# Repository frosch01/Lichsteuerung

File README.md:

# Lichtsteuerung

## Hardware setup

Prepare you PI for the S0-Shield by adding GPIO configuration to the config.txt.

```
echo "
# GPIO and PWM configuration for S0 shield
dtoverlay=pwm,pin=13,func=4,clock=500000
gpio=4,5,6,17,19,22,26,27=ip,pu
gpio=12,16,18,20,21,23,24,25=op,dh
" | sudo tee -a /boot/config.txt

```

For development, not using a PI Zero, a different IO setup is in use as Pins
of newer PI designs is different and there is a line collision with EPROM.

```
echo "
# GPIO and PWM configuration for S0 shield
dtoverlay=pwm,pin=13,func=4,clock=500000
gpio=15,5,6,17,19,22,26,27=ip,pu
gpio=12,16,18,20,21,23,24,25=op,dh
" | sudo tee -a /boot/config.txt
```

## Amount of Meter Pulses per year

One HVAC takes about 300kwh per year. This means 300k pulses. 3 HVAC systems 
result in <1M pulses per year.

In the log, a world timestamp, and the power shall be stored. The 
timestamp takes 11 bytes including space 11. The power takes 5 bytes including
newline. So 16 bytes to store. Let's go for 20 in calculation....

Amount of bytes expected per year: 20MByte

It seems to be feasible to keep a cache inside the program for online visualization.

Big data part should be kept separated from the tool.

For fast search a FS based directory structure based on year, and month with a file 
per day seems to be a valid data base idea.

TinyFLux seems to be a nice idea to use as a file based time series DB.

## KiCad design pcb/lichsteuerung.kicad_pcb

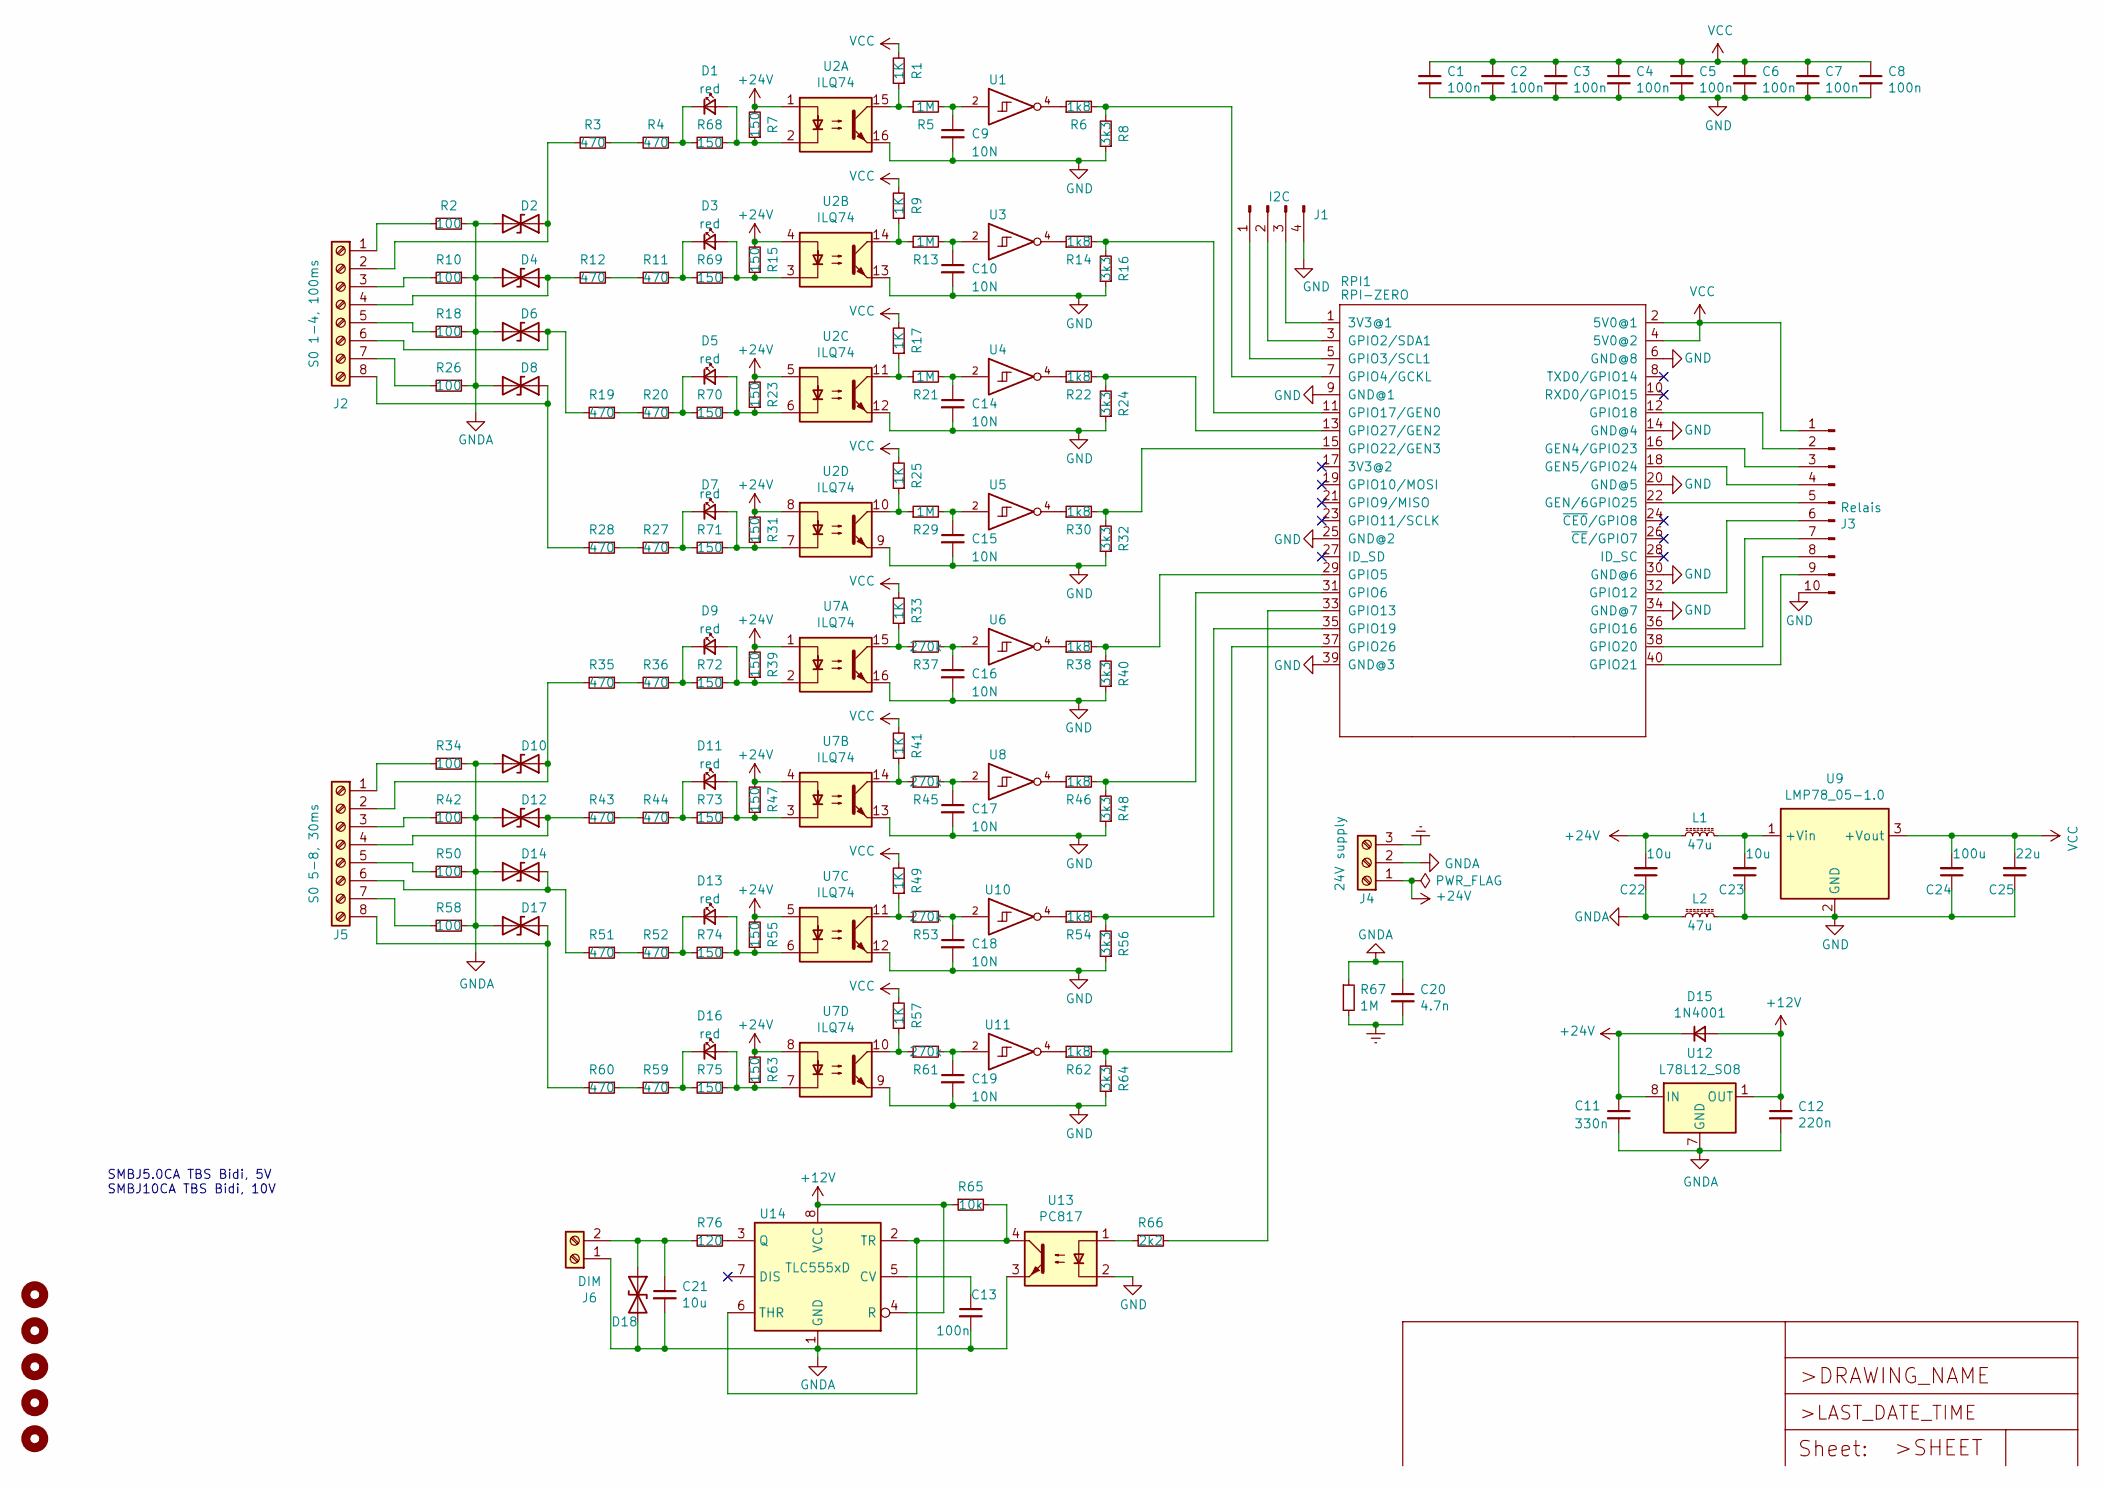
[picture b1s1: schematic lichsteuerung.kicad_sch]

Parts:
C1, C2, C3, C4, C5, C6, C7, C8, C13: 100n; C_0805_2012Metric_Pad1.18x1.45mm_HandSolder
C9, C10, C14, C15, C16, C17, C18, C19: 10N; C_0805_2012Metric_Pad1.18x1.45mm_HandSolder
C11: 330n; C_0805_2012Metric_Pad1.18x1.45mm_HandSolder
C12: 220n; C_0805_2012Metric_Pad1.18x1.45mm_HandSolder
C20: 4.7n; C_0805_2012Metric_Pad1.18x1.45mm_HandSolder
C21, C22, C23: 10u; C_1210_3225Metric_Pad1.33x2.70mm_HandSolder
C24: 100u; C_1210_3225Metric_Pad1.33x2.70mm_HandSolder
C25: 22u; C_1210_3225Metric_Pad1.33x2.70mm_HandSolder
D1, D3, D5, D7, D9, D11, D13, D16: red; LED_1206_3216Metric_Pad1.42x1.75mm_HandSolder
D2, D4, D6, D8, D10, D12, D14, D17: 24V; D_SMB
D15: 1N4001; D_SOD-123
D18: 12V; D_SMB
H1, H2, H3, H4, H5: MountingHole; MountingHole_3.2mm_M3_DIN965
J1: I2C; PinHeader_1x04_P2.54mm_Vertical
J2: S0 1-4, 100ms; TerminalBlock_Phoenix_MKDS-1,5-8-5.08_1x08_P5.08mm_Horizont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
J3: Relais; Molex_KK-254_AE-6410-10A_1x10_P2.54mm_Vertical
J4: 24V supply; TerminalBlock_Phoenix_MKDS-1,5-3-5.08_1x03_P5.08mm_Horizont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
J5: S0 5-8, 30ms; TerminalBlock_Phoenix_MKDS-1,5-8-5.08_1x08_P5.08mm_Horizont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
J6: DIM; TerminalBlock_Phoenix_MKDS-1,5-2-5.08_1x02_P5.08mm_Horizont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
L1, L2: 47u; L_1812_4532Metric_Pad1.30x3.40mm_HandSolder
R1, R9, R17, R25, R33, R41, R49, R57: 1K; R_0805_2012Metric_Pad1.20x1.40mm_HandSolder
R2, R10, R18, R26, R34, R42, R50, R58: 100; R_0805_2012Metric_Pad1.20x1.40mm_HandSolder
R3, R4, R11, R12, R19, R20, R27, R28, R35, R36, R43, R44, R51, R52, R59, R60: 470; R_1206_3216Metric_Pad1.30x1.75mm_HandSolder
R5, R13, R21, R29, R67: 1M; R_0805_2012Metric_Pad1.20x1.40mm_HandSolder
R6, R14, R22, R30, R38, R46, R54, R62: 1k8; R_0805_2012Metric_Pad1.20x1.40mm_HandSolder
R7, R15, R23, R31, R39, R47, R55, R63, R68, R69, R70, R71, R72, R73, R74, R75: 150; R_0805_2012Metric_Pad1.20x1.40mm_HandSolder
R8, R16, R24, R32, R40, R48, R56, R64: 3k3; R_0805_2012Metric_Pad1.20x1.40mm_HandSolder
R37, R45, R53, R61: 270k; R_0805_2012Metric_Pad1.20x1.40mm_HandSolder
R65: 10k; R_0805_2012Metric_Pad1.20x1.40mm_HandSolder
R66: 2k2; R_0805_2012Metric_Pad1.20x1.40mm_HandSolder
R76: 120; R_0805_2012Metric_Pad1.20x1.40mm_HandSolder
RPI1: RPI-ZERO; RASPBERRYPI_BASTELSTUBE_V13_RASPI_BOARD_ZERO_FULL
U1, U3, U4, U5, U6, U8, U10, U11: 74LVC1G14; SOT-23-5_HandSoldering
U2, U7: ILQ74; DIP-16_W7.62mm_LongPads
U9: LMP78_05-1.0; Converter_DCDC_Gaptech_LMx78_xx_1.0_THT
U12: L78L12_SO8; SOIC-8_3.9x4.9mm_P1.27mm
U13: PC817; DIP-4_W7.62mm_LongPads
U14: TLC555xD; SOIC-8_3.9x4.9mm_P1.27mm

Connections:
+12V: C12.1, D15.2 (A), R65.1, U12.1 (OUT), U14.4 (R), U14.8 (VCC)
+24V: C11.1, C22.2, D15.1 (K), J4.1, L1.1, R7.2, R15.2, R23.2, R31.2, R39.2, R47.2, R55.2, R63.2, U2.1, U2.4, U2.5, U2.8, U7.1, U7.4, U7.5, U7.8, U12.8 (IN)
Earth: C20.2, J4.3, R67.2
GND: C1.2, C2.2, C3.2, C4.2, C5.2, C6.2, C7.2, C8.2, C9.2, C10.2, C14.2, C15.2, C16.2, C17.2, C18.2, C19.2, C23.1, C24.1, C25.1, J1.4, J3.10, L2.2, R8.1, R16.1, R24.1, R32.1, R40.1, R48.1, R56.1, R64.1, RPI1.6 (GND@8), RPI1.9 (GND@1), RPI1.14 (GND@4), RPI1.20 (GND@5), RPI1.25 (GND@2), RPI1.30 (GND@6), RPI1.34 (GND@7), RPI1.39 (GND@3), U1.3 (GND), U2.9, U2.12, U2.13, U2.16, U3.3 (GND), U4.3 (GND), U5.3 (GND), U6.3 (GND), U7.9, U7.12, U7.13, U7.16, U8.3 (GND), U9.2 (GND), U10.3 (GND), U11.3 (GND), U13.2
GNDA: C11.2, C12.2, C13.2, C20.1, C21.2, C22.1, D2.2 (A2), D4.2 (A2), D6.2 (A2), D8.2 (A2), D10.2 (A2), D12.2 (A2), D14.2 (A2), D17.2 (A2), D18.2 (A2), J4.2, J6.1, L2.1, R2.1, R10.1, R18.1, R26.1, R34.1, R42.1, R50.1, R58.1, R67.1, U12.2 (GND), U12.3 (GND), U12.6 (GND), U12.7 (GND), U13.3, U14.1 (GND)
unnamed: C9.1, R5.2, U1.2
unnamed: C10.1, R13.2, U3.2
unnamed: C13.1, U14.5 (CV)
unnamed: C14.1, R21.2, U4.2
unnamed: C15.1, R29.2, U5.2
unnamed: C16.1, R37.2, U6.2
unnamed: C17.1, R45.2, U8.2
unnamed: C18.1, R53.2, U10.2
unnamed: C19.1, R61.2, U11.2
unnamed: C21.1, D18.1 (A1), J6.2, R76.2
unnamed: C23.2, L1.2, U9.1 (+Vin)
unnamed: D1.1 (K), R4.1, R68.2
unnamed: D1.2 (A), R7.1, R68.1, U2.2
unnamed: D2.1 (A1), J2.2, R3.2
unnamed: D3.1 (K), R11.1, R69.2
unnamed: D3.2 (A), R15.1, R69.1, U2.3
unnamed: D4.1 (A1), J2.4, R12.2
unnamed: D5.1 (K), R20.1, R70.2
unnamed: D5.2 (A), R23.1, R70.1, U2.6
unnamed: D6.1 (A1), J2.6, R19.2
unnamed: D7.1 (K), R27.1, R71.2
unnamed: D7.2 (A), R31.1, R71.1, U2.7
unnamed: D8.1 (A1), J2.8, R28.2
unnamed: D9.1 (K), R36.1, R72.2
unnamed: D9.2 (A), R39.1, R72.1, U7.2
unnamed: D10.1 (A1), J5.2, R35.2
unnamed: D11.1 (K), R44.1, R73.2
unnamed: D11.2 (A), R47.1, R73.1, U7.3
unnamed: D12.1 (A1), J5.4, R43.2
unnamed: D13.1 (K), R52.1, R74.2
unnamed: D13.2 (A), R55.1, R74.1, U7.6
unnamed: D14.1 (A1), J5.6, R51.2
unnamed: D16.1 (K), R59.1, R75.2
unnamed: D16.2 (A), R63.1, R75.1, U7.7
unnamed: D17.1 (A1), J5.8, R60.2
unnamed: J1.1, RPI1.5 (GPIO3/SCL1)
unnamed: J1.2, RPI1.3 (GPIO2/SDA1)
unnamed: J1.3, RPI1.1 (3V3@1)
unnamed: J2.3, R10.2
unnamed: J2.5, R18.2
unnamed: J2.7, R26.2
unnamed: J5.1, R34.2
unnamed: J5.3, R42.2
unnamed: J5.5, R50.2
unnamed: J5.7, R58.2
unnamed: R1.1, R5.1, U2.15
unnamed: J2.1, R2.2
unnamed: R3.1, R4.2
unnamed: R6.1, U1.4
unnamed: R6.2, R8.2, RPI1.7 (GPIO4/GCKL)
unnamed: R11.2, R12.1
unnamed: R9.1, R13.1, U2.14
unnamed: R14.1, U3.4
unnamed: R14.2, R16.2, RPI1.11 (GPIO17/GEN0)
unnamed: R17.1, R21.1, U2.11
unnamed: R19.1, R20.2
unnamed: R22.1, U4.4
unnamed: R22.2, R24.2, RPI1.13 (GPIO27/GEN2)
unnamed: R25.1, R29.1, U2.10
unnamed: R27.2, R28.1
unnamed: R30.1, U5.4
unnamed: R30.2, R32.2, RPI1.15 (GPIO22/GEN3)
unnamed: R33.1, R37.1, U7.15
unnamed: R35.1, R36.2
unnamed: R38.1, U6.4
unnamed: R38.2, R40.2, RPI1.29 (GPIO5)
unnamed: R41.1, R45.1, U7.14
unnamed: R43.1, R44.2
unnamed: R46.1, U8.4
unnamed: R46.2, R48.2, RPI1.31 (GPIO6)
unnamed: R49.1, R53.1, U7.11
unnamed: R51.1, R52.2
unnamed: R54.1, U10.4
unnamed: R54.2, R56.2, RPI1.35 (GPIO19)
unnamed: R57.1, R61.1, U7.10
unnamed: R59.2, R60.1
unnamed: R62.1, U11.4
unnamed: R62.2, R64.2, RPI1.37 (GPIO26)
unnamed: R65.2, U13.4, U14.2 (TR), U14.6 (THR)
unnamed: R66.1, U13.1
unnamed: R66.2, RPI1.33 (GPIO13)
unnamed: R76.1, U14.3 (Q)
unnamed: J3.2, RPI1.12 (GPIO18)
unnamed: J3.3, RPI1.16 (GEN4/GPIO23)
unnamed: J3.4, RPI1.18 (GEN5/GPIO24)
unnamed: J3.5, RPI1.22 (GEN/6GPIO25)
unnamed: J3.6, RPI1.32 (GPIO12)
unnamed: J3.7, RPI1.36 (GPIO16)
unnamed: J3.8, RPI1.38 (GPIO20)
unnamed: J3.9, RPI1.40 (GPIO21)
VCC: C1.1, C2.1, C3.1, C4.1, C5.1, C6.1, C7.1, C8.1, C24.2, C25.2, J3.1, R1.2, R9.2, R17.2, R25.2, R33.2, R41.2, R49.2, R57.2, RPI1.2 (5V0@1), RPI1.4 (5V0@2), U1.5 (VCC), U3.5 (VCC), U4.5 (VCC), U5.5 (VCC), U6.5 (VCC), U8.5 (VCC), U9.3 (+Vout), U10.5 (VCC), U11.5 (VCC)

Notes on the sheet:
SMBJ5.0CA TBS Bidi, 5V SMBJ10CA TBS Bidi, 10V

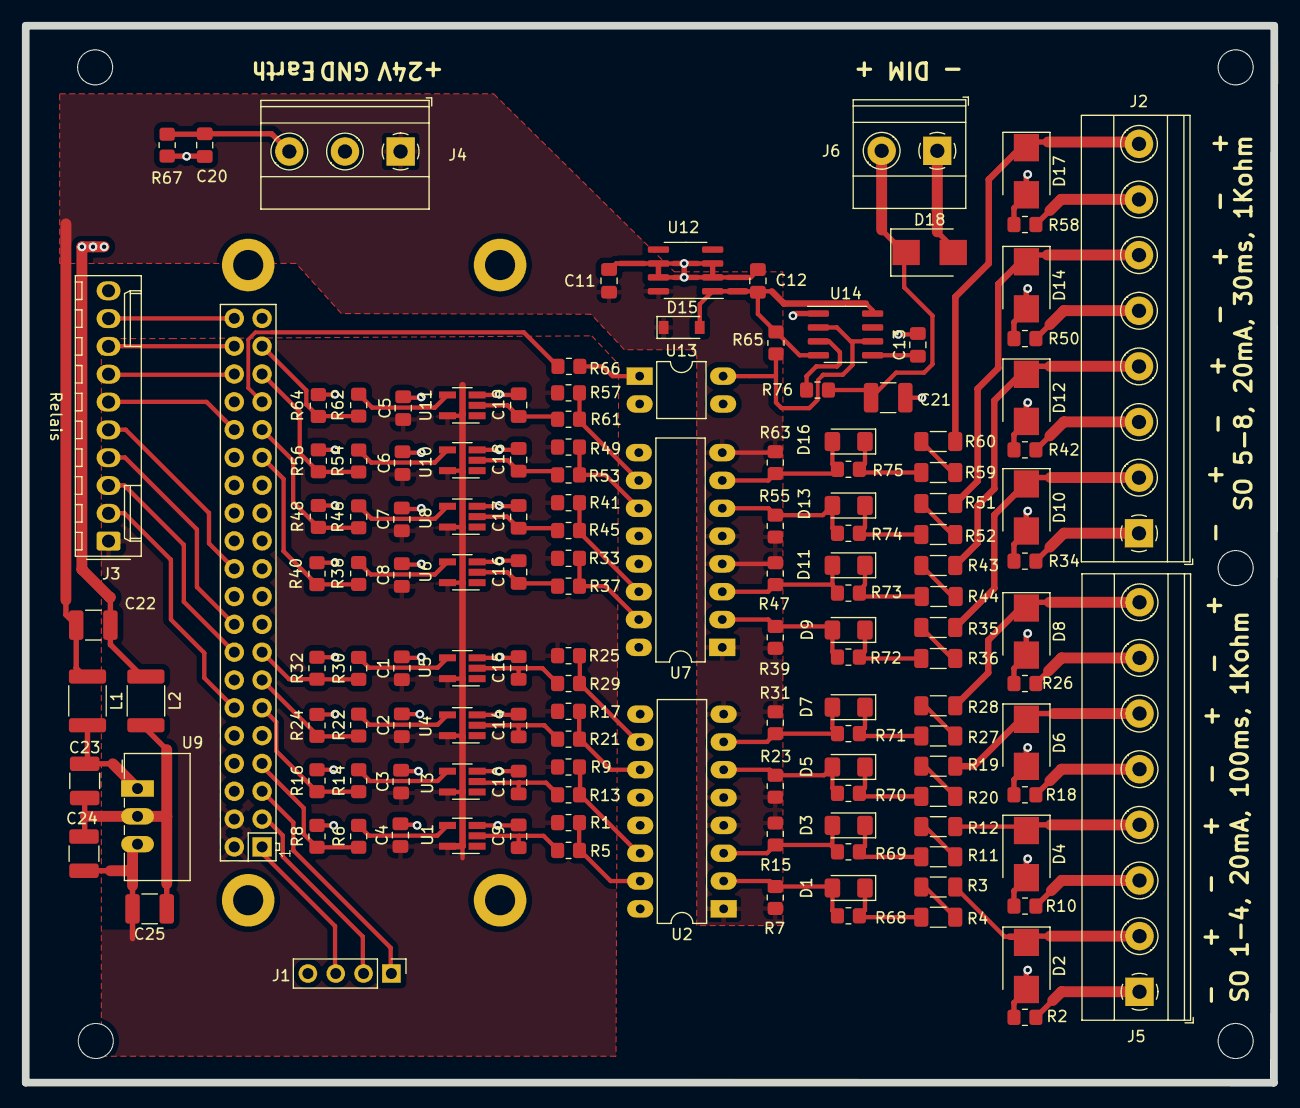
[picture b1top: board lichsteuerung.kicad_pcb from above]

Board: 2 copper layers, 114.0 x 96.5 mm, 147 parts (0 on the bottom side), 96 nets.

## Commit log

2017-06-14 ADDED: Test script for relais test
2017-06-15 ADDED: Readme.md, empty for now
2017-06-15 ADDED: little pwm test
2017-06-18 ADDED: Python based device access using wiringpi
2017-06-27 CHANGED: Design adapted towards better OO concepts. A singleton aproach seems to meet basic IO best
2017-06-27 CHANGED: Design to be more pythonic and more object oriented.
2017-06-27 FIXED: Removed vertical spaces
2017-06-27 CHANGED: Removed dependency from global gpio object.
2017-07-02 ADDED: Simple test from flexx button API documentation.
2017-07-02 CHANGED: Location of test/demo programs
2017-07-02 CHANGED: Switch to Python asyncio event handling
2017-07-02 CHANGED: Timing changed to absolute timing
2017-07-03 CHANGED: Relais timed on state implemented into own class
2017-07-03 ADDED: Added time until relais On
2017-07-05 ADDED: First Web UI
2017-07-07 ADDED: Stub GPIO module to be able to also run on X86
2017-07-07 FIXED. Py detection
2017-07-07 ADDED: Threading for asyncio GPIO
2017-07-07 FIXED: Exiting
2017-07-07 ADDED: print
2017-07-08 CHANGED: GPIO instance belongs now to LightControl
2017-07-08 FIXED: Missing file from previous commit.
2017-07-08 CHANGED: Main moved into light_ui.py for easier connecting UI with light_control
2017-07-09 ADDED: Made light_control to react on light UI.
2017-07-09 CHANGED: Switched to using events instead of properties as event are more versatile
2017-07-09 FIXED: Auto mode is default off
2017-07-09 ADDED: Enhanced event handling to all the Lamps
2017-07-09 FIXED: Override behavior of automatic mode
2017-07-09 ADDED: Action log printing
2017-07-09 ADDED: Handling of detectors from UI
2017-07-09 FIXED: variable referencing
2017-07-09 ADDED: PWM initialized
2017-07-09 FIXED: Bad parameters
2017-07-09 ADDED: PWM support. Needs root to execute
2017-07-10 CHANGED: Flexx Events are now handled by Python class instead of JS class
2017-07-10 ADDED: Determination of night and day from clock
2017-08-08 ADDED: Reflect current mode as UI is started
2017-08-09 CHANGED: Lamp to relais assignment
2017-08-09 CHANGED: Input assignment
2017-08-09 CHANGED: PWM range
2017-08-09 ADDED: Light activation limited to night!
2017-08-10 ADDED: Setting of default modes at 06:00
2017-08-10 FIXED: Made output unbuffered to get outputs immediatly into system logs when runniung as daemon
2023-01-06 Added updated PCB
2023-01-06 Added .gitignore
2023-12-25 Add documentation how RPI HW setup
2023-12-25 Run pylint, clear errors
    Focus is given to class IoControl which is intended to be pushed into a
    separate module.
2024-01-04 ✨ Add io_control for new HW shield
    Implemented based on Python 3.11 and gpiod using libgpiod 2.1.x.
2024-01-04 Create pylint.yml
    Add runner for pylint
2024-01-04 Create python-app.yml
    Add pytest CI automation
2024-01-04 ✨ Add s0 energy metering
    S0 is a pulse based interface. It is found on many energy meters. The
    implementation is based on a software counter. By derivating the pulses
    over time, the power consumption is calculated.
2024-01-04 💚 Fix python application workflow
    Fixed:
    - missing mock package
2024-01-05 🚚 Push low level GPIO into dedicated class
    Part 1 of separating low level access and high level acces of I/O control
    into 2 classes.
2024-02-03 ♻️ Refactor GpioMap and prepare for testing
    Focus on low level I/O only. Remove all async code from the class. Add
    API documentation.
2024-02-03 ✅ Add GpioMap testing
    Add test for low level HW access testing. Tests will only run on HW
    that has a shield connected. Also, the S0 inputs must be connected to
    the relais.
2024-02-03 ⚗️ Add experiment for fast list member check
    What is faster? Using 'in' on a list directly or via a helper dict.
2024-02-03 💚 Fix CI after refactoring
2024-02-03 🏗️ Re-add io_control.py as 2nd level abstraction
    io_control shall take the job to distinguish detector and meter inputs
    and provide asyncio interfaces as required.
2024-02-03 ✨ Add UI based on nicegui
2024-02-03 ✨ Integrate meter with IoControl
2024-02-03 📝 Add some thoughts on logging
2024-02-03 ⚗️ Verify approach of I/O thread
2024-02-03 ✨ Add new class Timespan
    Timespan is intended to represent a span of time given by a start point
    and an end point in time. It can be used with any clock.
2024-02-03 🧵 Add asyncio interface to S0Meter class
    Add ayncio.Queue based processing of S0Events.
2024-02-03 🧵 Convert IoControl into generic S0Eventhandler
    Provide an async integration of meters with s0 event handler.
2024-02-03 ✨ Add TimedRelais class
    TimedRelais is a class to turn relais on and off given by a timed
    schedule.
2024-02-03 💡 Add documentation on modules and classes
    More words on s0_meter.py and io_control.py.
2024-02-03 ♻️ Spawn event handler tasks implicitly
    Having all these event handler tasks at the top level is anoying. Tasks
    are spawned implicitly by __init__.
2024-02-03 ✨ Add time/location based sun sensor
    A daylight sensor based on the idea that sunset and sunrise can be
    determined by location and local time.
2024-04-07 ✨ Couple UI with I/O
    First working new design. As of now, based on a global/singleton
    based architecture, but all features from the previous implementation
    are included.
2024-04-07 🧱 Add systemd service file
    The light-control shall be executed automatically on boot.
2024-04-07 🩹 Adapt on times of lamps
    The former values have been set for playing in lab. On times
    were very short which creates high wear on LED lights. Longer
    on times will let last lamps longer.
2024-05-26 ✨ Add storing of meters in state file
    Application states are stored at /var/lib/light-control/state.json.
2024-05-26 ✨ Add calibration inputs to UI
    It is convenient to read the meters and directly input the displayed
    values as calibration value for the local energy counters.
2024-05-26 ✨ Add dimmer support
    Lamp on terrace has a dimmer. Enable dimming. UI had already the
    element, however it was just an UI element.
2024-05-26 🔥 Remove obsolte files
2024-05-26 ✅ Add test
    More tests added
2024-05-26 🩹 Increaded on times for lamps
    LED lights have limited number of on-off cycles. Increaing the times
    reduces the wear of lamps.
2024-05-26 🙈 Update .gitignore
2024-06-22 ✨ Add detection of board version
    PI Zero and regular PI boards have a different assignment of GPIO Pins.
    Unfortuately, one PIN was selected on Zero that was not available on
    PI4. So a Board_type detection was added.
2024-06-22 ⚗️ Add some basic API checks
    Add some little examples on how to deal with asyncio events (SW) and
    how to use the Raspi HW PWM.
2024-06-22 🚚 Rename directory test into experiments
2024-06-22 ⬆️ Update requirments.txt
2026-01-02 🐛 Fix instantiation if light_ui singleton
    This fix was required due to a change of upstream nicegui.
2026-01-02 ✨ Add MQTT client
    A client is added, for now to publish topics for motion detectors.
2026-01-02 💚 Make use of uv tool for project management
    uv is the new star for project management.
2026-01-03 ✨ Change behavior of sun events
    Sun events shall no longer enable or disable the detectors
    rather than directly enabling or dsabling the relais/lamps.
2026-01-03 👷 Add packaging support for nicegui-pack
    It is a mess to get the light control running on target
    PI zero W due to too many dempendencies that can not be
    compiled on the PI zero. Enabling a packaging will be the
    way to deploy the SW.
2026-01-31 👽️ Adapted to latest nicegui app design
    Pages became a central component of nicegui. Add a single
    root page that is used to render UI.
2026-01-31 ⬇️ Remove dependency to rpi-version
    RPI version package is of minor use and not really
    well maintained. Newer PI HW version are not supported.
    Just reading /proc/device-tree/model is the preferred
    solution.
2026-01-31 📝 Add documentation fur using PI4
    PI4 has some other demand to IO mappings. Add documentation
2026-02-21 🩹 Add retries for HW PWM
    After updating PI, the HW pwm raises permission denied. By doing
    a retry, things have been mitigated.
2026-02-22 🚀 Use uv also for executing service
    The usage of uv is also brought to service execution.
2026-02-24 ✨ Add UI tabs for Fluffy and Solar
    Externd UI with tabs for controlling fluffy and an
    iframe to display solar UI in tab.
